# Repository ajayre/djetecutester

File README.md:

# D-Jetronic ECU Tester

A board for testing D-Jetronic ECUs installed on Mercedes C/R107 vehicles.

No warranty, express or implied. Use at your own risk.

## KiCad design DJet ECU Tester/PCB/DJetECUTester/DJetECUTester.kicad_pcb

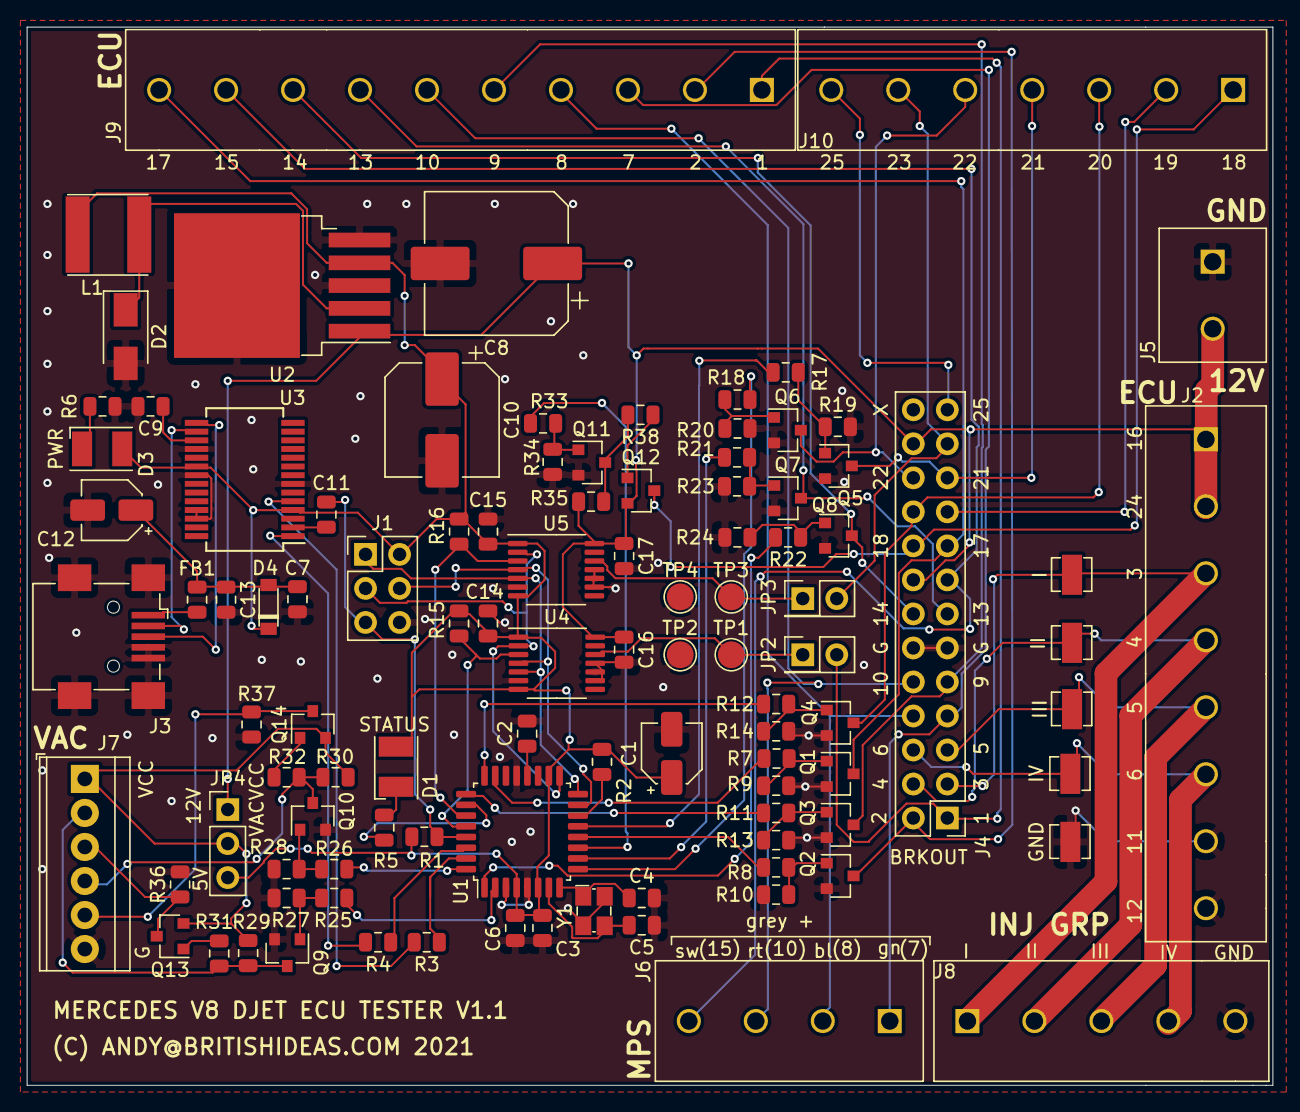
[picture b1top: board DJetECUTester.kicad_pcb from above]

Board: 2 copper layers, 93.0 x 79.0 mm, 103 parts (0 on the bottom side), 81 nets.

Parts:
C1: 4.7uF e; CP_Elec_4x5.8
C2, C9, C11, C13, C14, C15, C16, C17: 100nF; C_0805_2012Metric
C3, C6: 1uF; C_0805_2012Metric
C4, C5: 18pF; C_0805_2012Metric
C7: 10nF; C_0805_2012Metric
C8: 680uF e; CP_Elec_10x10.5
C10: 220uF e; CP_Elec_8x6.5
C12: 4.7uF 16V e; CP_Elec_4x5.8
D1: RED; LED_PLCC-2
D2: B360A-13-F; D_SMA
D3: PWR; LED_PLCC-2
D4: MBR0520LT1G; SOD-123
FB1: MI0805K400R-10; R_0805_2012Metric
J1: ISP; PinHeader_2x03_P2.54mm_Vertical
J2: ECU1; PhoenixContact_COMBICON_PT_8
J3: USB_B_Mini; USB_Mini-B_Wuerth_65100516121_Horizontal
J4: BREAKOUT; PinHeader_2x13_P2.54mm_Vertical
J5: 12V IN; PhoenixContact_COMBICON_MKDSN_2
J6: MPS; PhoenixContact_COMBICON_PT_4
J7: VAC; TerminalBlock_TE_282834-6_1x06_P2.54mm_Horizontal
J8: INJECTORS; PhoenixContact_COMBICON_PT_5
J9: ECU2; PhoenixContact_COMBICON_PT_10
J10: ECU3; PhoenixContact_COMBICON_PT_7
JP2: AIRTEMP; PinHeader_2x01_P2.54mm_Vertical
JP3: COOLANTTEMP; PinHeader_2x01_P2.54mm_Vertical
JP4: VAC VCC; PinHeader_1x03_P2.54mm_Vertical
L1: 33uH; Wurth-WE-LQS-Inductor
Q1, Q2, Q3, Q4, Q5, Q6, Q7, Q8, Q9, Q10, Q11: MMBT2222ALT1G; SOT-23
Q12, Q13, Q14: MMBT3906LT1G; SOT-23
R1, R2, R3, R4, R5, R6: 1K; R_0805_2012Metric
R7, R8, R11, R12, R17, R18, R21, R22, R25, R26, R31, R32, R33, R38: 1k; R_0805_2012Metric
R9, R10, R13, R14, R19, R20, R23, R24, R27, R28, R29, R30, R34, R35, R36, R37: 10k; R_0805_2012Metric
R15, R16: 100k; R_0805_2012Metric
TP1, TP2, TP3, TP4: TestPoint; TestPoint_Pad_D2.0mm
TP5, TP6, TP7, TP8: 5194TR; 5190TR-Colored-Test-Point
TP9: 5195TR; 5190TR-Colored-Test-Point
U1: ATmega328P; LQFP-32_7x7mm_P0.8mm
U2: LM2596S-5; TO-263-5_TabPin3
U3: FT232RL; SSOP-28_5.3x10.2mm_P0.65mm
U4, U5: MCP41HV51-502E-ST; TSSOP-14_4.4x5mm_P0.65mm
Y1: FA-238 16.0000MB-C3; FA-238

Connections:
+3V3: C9.1, U3.17
+5V: C1.1, C3.1, C6.1, C10.1, C14.1, C15.1, D1.2, D3.2, D4.1, J1.2, JP4.3, L1.2, R1.1, R2.1, R15.1, R16.1, U1.4, U1.6, U1.18, U2.4, U3.4, U3.20, U4.1, U4.7, U5.1, U5.7
+12V: C8.1, C16.1, C17.1, J2.1, J2.2, J4.16, J4.24, J5.2, JP4.1, Q12.2, R35.1, U2.1, U4.14, U5.14
/ECU_AIRTEMP-1: J4.1, J9.1, JP2.2
/ECU_COOLANTTEMP-23: J4.23, J10.6, JP3.2
/ECU_DIAGGROUP13-25: J4.25, J10.7
/ECU_FUELPUMPRELAY-19: J4.19, J10.2
/ECU_INJGROUP1-3: J2.3, J4.3, J8.1, TP5.1
/ECU_INJGROUP2-4: J2.4, J4.4, J8.2, TP6.1
/ECU_INJGROUP3-5: J2.5, J4.5, J8.3, TP7.1
/ECU_INJGROUP4-6: J2.6, J4.6, J8.4, TP8.1
/ECU_START-18: J4.18, J10.1, Q12.3
/ECU_TPSACCEL1-9: J4.9, J9.5, Q3.3
/ECU_TPSACCEL2-20: J4.20, J10.3, Q4.3
/ECU_TPSIDLE-17: J4.17, J9.10, Q1.3
/ECU_TPSWOT-2: J4.2, J9.2, Q2.3
/ECU_TRIGGERGROUP1-21: J4.21, J10.4, Q5.3
/ECU_TRIGGERGROUP2-13: J4.13, J9.7, Q7.3
/ECU_TRIGGERGROUP3-22: J4.22, J10.5, Q6.3
/ECU_TRIGGERGROUP4-14: J4.14, J9.8, Q8.3
/MISO: J1.1, U1.16, U4.5, U5.5
/MOSI: J1.4, U1.15, U4.4, U5.4
/MPS-7: J4.7, J6.1, J9.3
/MPS-8: J4.8, J6.2, J9.4
/MPS-10: J4.10, J6.3, J9.6
/MPS-15: J4.15, J6.4, J9.9
/RX: R4.2, U3.1
/SCK: J1.3, U1.17, U4.2, U5.2
/START: R33.2, U1.11
/STATUS: R5.2, U1.26
/TPSACCEL1: R11.2, U1.25
/TPSACCEL2: R12.2, U1.24
/TPSIDLE: R7.2, U1.23
/TPSWOT: R8.2, U1.12
/TRIGGERGROUP1: R17.2, U1.13
/TRIGGERGROUP2: R18.2, U1.9
/TRIGGERGROUP3: R21.2, U1.10
/TRIGGERGROUP4: R22.2, U1.1
/TX: R3.2, U3.5
/VAC1: R25.2, U1.2
/VAC2: R26.2, U1.32
/Vacuum/VACVCC: J7.1, JP4.2, Q13.2, Q14.2, R29.1, R30.1
/~AIRTEMP_CS: R15.2, U1.28, U4.3
/~COOLANTTEMP_CS: R16.2, U1.27, U5.3
/~RESET: C11.1, J1.5, R1.2, U1.29
GND: C1.2, C2.2, C3.2, C4.2, C5.1, C6.2, C7.1, C8.2, C9.2, C10.2, C12.2, C13.2, C14.2, C15.2, C16.2, C17.2, D2.2, J1.6, J2.7, J2.8, J3.4, J3.5, J3.6, J4.11, J4.12, J5.1, J7.6, J8.5, Q1.2, Q2.2, Q3.2, Q4.2, Q5.2, Q6.2, Q7.2, Q8.2, Q9.2, Q10.2, Q11.2, R6.1, R9.2, R10.2, R13.2, R14.2, R19.2, R20.2, R23.2, R24.2, R27.2, R28.2, R34.2, R36.2, R37.2, TP2.1, TP4.1, TP9.1, U1.3, U1.5, U1.21, U2.3, U2.5, U3.7, U3.18, U3.21, U3.25, U3.26, U4.6, U4.9, U4.10, U4.11, U5.6, U5.9, U5.10, U5.11, Y1.2, Y1.4
unnamed: C2.1, U1.20
unnamed: C4.1, U1.8, Y1.1
unnamed: C5.2, U1.7, Y1.3
unnamed: C11.2, U3.2
unnamed: D1.1, R5.1
unnamed: D2.1, L1.1, U2.2
unnamed: D3.1, R6.2
unnamed: FB1.1, J3.1
unnamed: J3.2, U3.16
unnamed: J3.3, U3.15
unnamed: J7.2, Q9.3, R29.2, R31.2
unnamed: J7.3, Q13.3, R36.1
unnamed: J7.4, Q10.3, R30.2, R32.2
unnamed: J7.5, Q14.3, R37.1
unnamed: JP2.1, TP1.1, U4.12
unnamed: JP3.1, TP3.1, U5.12
unnamed: Q1.1, R7.1, R9.1
unnamed: Q2.1, R8.1, R10.1
unnamed: Q3.1, R11.1, R13.1
unnamed: Q4.1, R12.1, R14.1
unnamed: Q5.1, R17.1, R19.1
unnamed: Q6.1, R18.1, R20.1
unnamed: Q7.1, R21.1, R23.1
unnamed: Q8.1, R22.1, R24.1
unnamed: Q9.1, R25.1, R27.1
unnamed: Q10.1, R26.1, R28.1
unnamed: Q11.1, R33.1, R34.1
unnamed: Q11.3, R35.2, R38.2
unnamed: Q12.1, R38.1
unnamed: Q13.1, R31.1
unnamed: Q14.1, R32.1
unnamed: R2.2, U1.14
unnamed: R3.1, U1.31
unnamed: R4.1, U1.30
VBUS: C7.2, C12.1, C13.1, D4.2, FB1.2

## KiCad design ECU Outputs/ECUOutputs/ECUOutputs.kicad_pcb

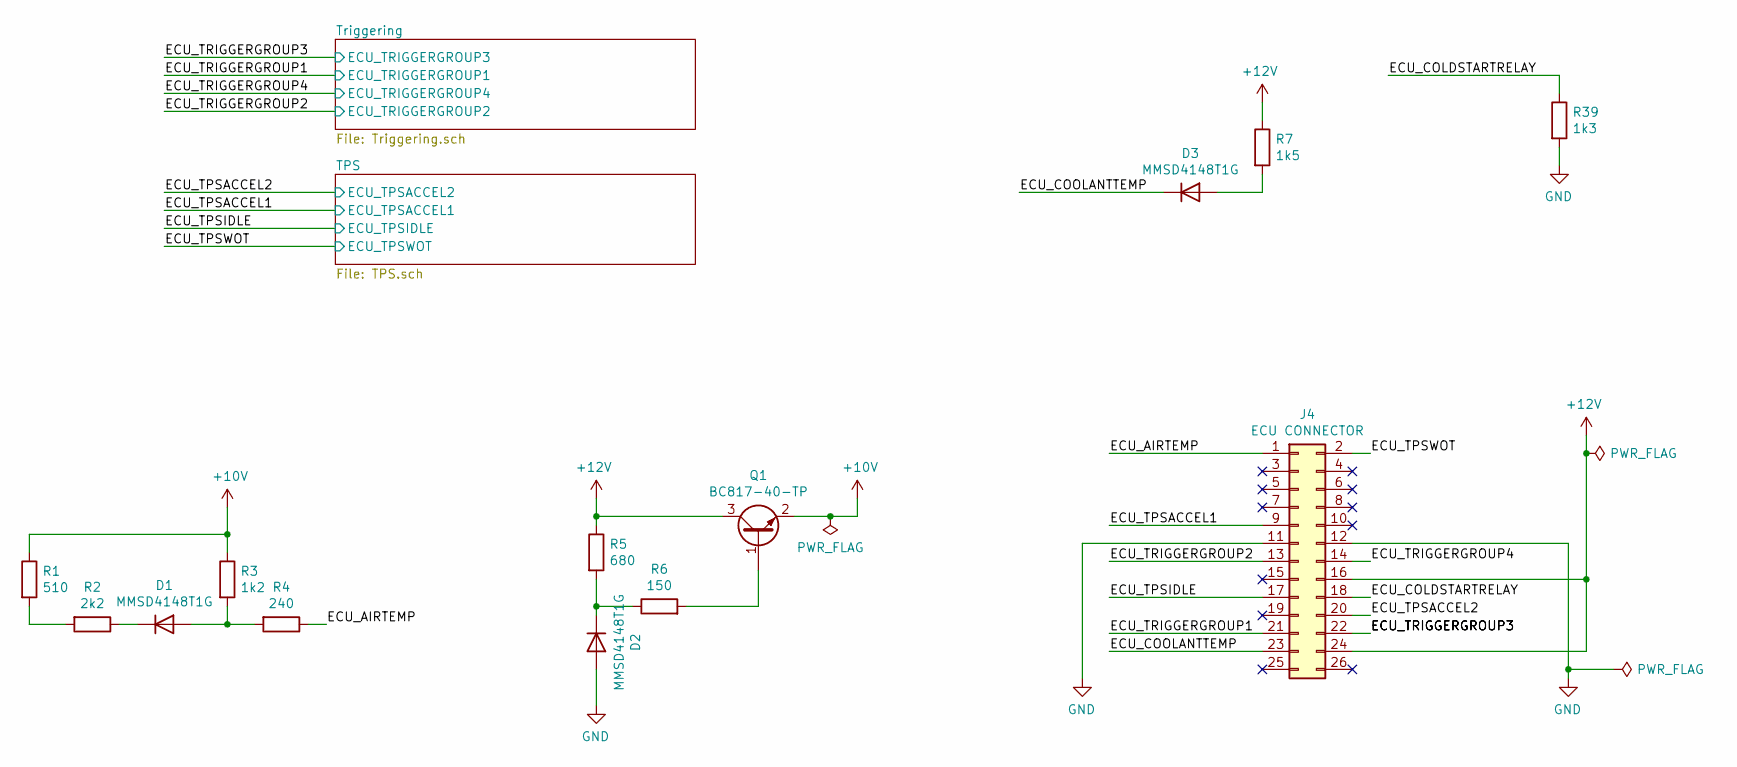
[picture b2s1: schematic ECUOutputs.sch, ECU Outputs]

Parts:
D1, D2, D3: MMSD4148T1G; D_SOD-123
J4: ECU CONNECTOR; IDC-Header_2x13_P2.54mm_Vertical
Q1: BC817-40-TP; SOT-23
R1: 510; R_0805_2012Metric
R2: 2k2; R_0805_2012Metric
R3: 1k2; R_0805_2012Metric
R4: 240; R_0805_2012Metric
R5: 680; R_0805_2012Metric
R6: 150; R_0805_2012Metric
R7: 1k5; R_0805_2012Metric
R39: 1k3; R_0805_2012Metric

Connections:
+10V: Q1.2 (E), R1.1, R3.1; also elsewhere on the board
+12V: J4.16, J4.24, Q1.3 (C), R5.1, R7.1; also elsewhere on the board
/ECU_AIRTEMP: J4.1, R4.1
/ECU_COLDSTARTRELAY: J4.18, R39.1
/ECU_COOLANTTEMP: D3.1 (K), J4.23
/ECU_TPSACCEL1: J4.9; also elsewhere on the board
/ECU_TPSACCEL2: J4.20; also elsewhere on the board
/ECU_TPSIDLE: J4.17; also elsewhere on the board
/ECU_TPSWOT: J4.2; also elsewhere on the board
/ECU_TRIGGERGROUP1: J4.21; also elsewhere on the board
/ECU_TRIGGERGROUP2: J4.13; also elsewhere on the board
/ECU_TRIGGERGROUP3: J4.22; also elsewhere on the board
/ECU_TRIGGERGROUP4: J4.14; also elsewhere on the board
GND: D2.2 (A), J4.11, J4.12, R39.2; also elsewhere on the board
unnamed: D1.1 (K), R2.1
unnamed: D1.2 (A), R3.2, R4.2
unnamed: D2.1 (K), R5.2, R6.1
unnamed: D3.2 (A), R7.2
unnamed: Q1.1 (B), R6.2
unnamed: R1.2, R2.2

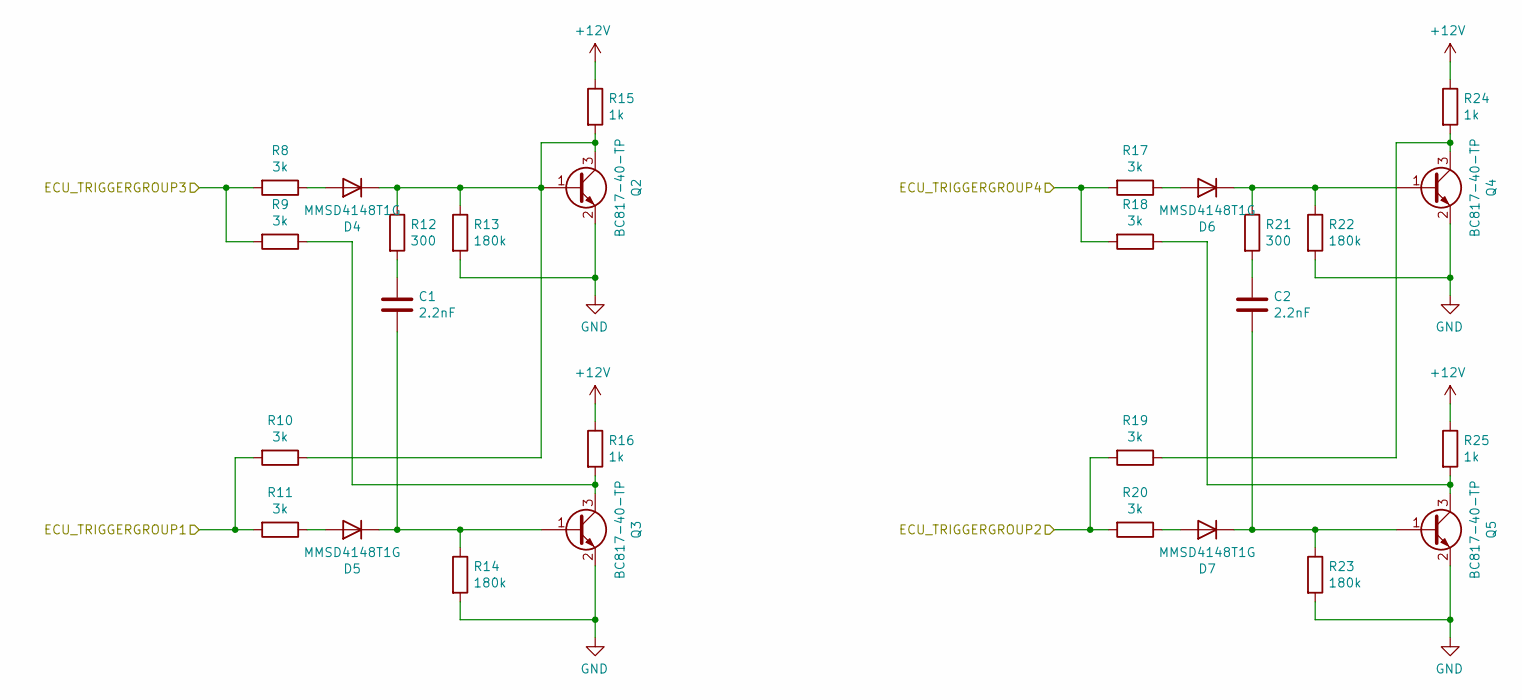
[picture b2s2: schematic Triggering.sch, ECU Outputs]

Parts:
C1, C2: 2.2nF; C_0805_2012Metric
D4, D5, D6, D7: MMSD4148T1G; D_SOD-123
Q2, Q3, Q4, Q5: BC817-40-TP; SOT-23
R8, R9, R10, R11, R17, R18, R19, R20: 3k; R_0805_2012Metric
R12, R21: 300; R_0805_2012Metric
R13, R14, R22, R23: 180k; R_0805_2012Metric
R15, R16, R24, R25: 1k; R_0805_2012Metric

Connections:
+12V: R15.1, R16.1, R24.1, R25.1; also elsewhere on the board
/ECU_TRIGGERGROUP1: R10.2, R11.2; also elsewhere on the board
/ECU_TRIGGERGROUP2: R19.2, R20.2; also elsewhere on the board
/ECU_TRIGGERGROUP3: R8.2, R9.2; also elsewhere on the board
/ECU_TRIGGERGROUP4: R17.2, R18.2; also elsewhere on the board
GND: Q2.2 (E), Q3.2 (E), Q4.2 (E), Q5.2 (E), R13.2, R14.2, R22.2, R23.2; also elsewhere on the board
unnamed: C1.1, R12.2
unnamed: C1.2, D5.1 (K), Q3.1 (B), R14.1
unnamed: C2.1, R21.2
unnamed: C2.2, D7.1 (K), Q5.1 (B), R23.1
unnamed: D4.1 (K), Q2.1 (B), Q2.3 (C), R10.1, R12.1, R13.1, R15.2
unnamed: D4.2 (A), R8.1
unnamed: D5.2 (A), R11.1
unnamed: D6.1 (K), Q4.1 (B), R21.1, R22.1
unnamed: D6.2 (A), R17.1
unnamed: D7.2 (A), R20.1
unnamed: Q3.3 (C), R9.1, R16.2
unnamed: Q4.3 (C), R19.1, R24.2
unnamed: Q5.3 (C), R18.1, R25.2

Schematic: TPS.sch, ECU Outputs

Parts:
C3: 3.3nF
D8, D9, D10, D11, D12: D
Q6, Q7: Q_NPN_BCE
Q8: Q_PNP_BCE
R26, R29: 3k
R27, R28: 10k
R30, R31: 180k
R32: 300
R33, R34: 1k8
R35: 47k
R36: 5k1
R37: 22k
R38: 6k2

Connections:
+10V: Q8.3, R36.1, R37.1; also elsewhere on the board
+12V: R33.1, R34.1; also elsewhere on the board
/ECU_TPSACCEL1: R28.2, R29.2; also elsewhere on the board
/ECU_TPSACCEL2: R26.2, R27.2; also elsewhere on the board
/ECU_TPSIDLE: D11.1 (K), D12.1 (K); also elsewhere on the board
/ECU_TPSWOT: R36.2; also elsewhere on the board
GND: D11.2 (A), Q6.2, Q7.2, R30.2, R31.2, R38.2; also elsewhere on the board
unnamed: C3.1, R32.2
unnamed: C3.2, D10.1 (K), Q7.1, R31.1
unnamed: D8.1 (K), Q6.1, R30.1, R32.1
unnamed: D8.2 (A), R26.1
unnamed: D9.2 (A), R29.1
unnamed: D9.1 (K), D10.2 (A)
unnamed: D12.2 (A), R35.1
unnamed: Q6.3, R28.1, R33.2
unnamed: Q7.3, R27.1, R34.2
unnamed: Q8.1, R35.2, R37.2
unnamed: Q8.2, R38.1

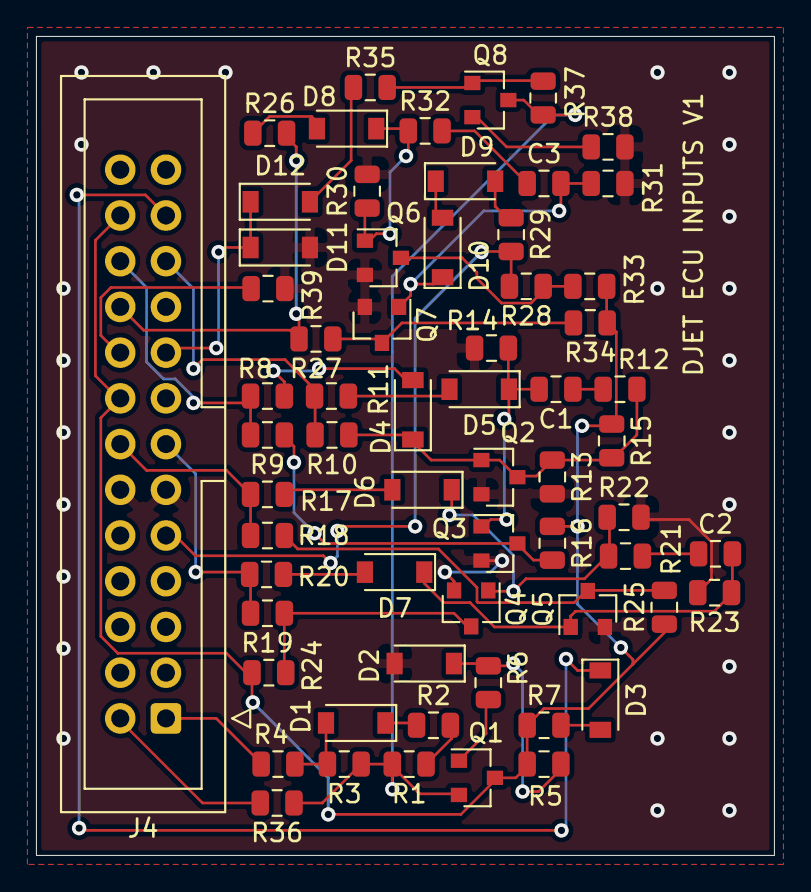
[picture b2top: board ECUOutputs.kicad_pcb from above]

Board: 2 copper layers, 41.0 x 45.5 mm, 63 parts (0 on the bottom side), 44 nets.

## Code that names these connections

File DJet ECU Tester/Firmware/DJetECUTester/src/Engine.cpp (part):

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// pins
#define PIN_STATUS_LED    A3  // PC3
#define PIN_START         7   // PD7
#define PIN_TPSWOT        8   // PB0
#define PIN_TPSIDLE       A0  // PC0
#define PIN_TPSACCEL1     A2  // PC2
#define PIN_TPSACCEL2     A1  // PC1
#define PIN_VAC1          4   // PD4
#define PIN_VAC2          2   // PD2
#define PIN_AIRTEMPCS     A5  // PC5
#define PIN_COOLANTTEMPCS A4  // PC4

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#define PORT_TRIGGERGROUP3 PORTD
#define PORT_TRIGGERGROUP4 PORTD

#define PIN_TRIGGERGROUP1 1
#define PIN_TRIGGERGROUP2 6
#define PIN_TRIGGERGROUP3 5
#define PIN_TRIGGERGROUP4 3

#define DIR_TRIGGERGROUP1 DDRB
#define DIR_TRIGGERGROUP2 DDRD
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#define STARTING               digitalWrite(PIN_START, HIGH);
#define NOTSTARTING            digitalWrite(PIN_START, LOW);

#define TPS_WOT                digitalWrite(PIN_TPSWOT, HIGH);
#define TPS_NOTWOT             digitalWrite(PIN_TPSWOT, LOW);

#define TPS_IDLE               digitalWrite(PIN_TPSIDLE, HIGH);
#define TPS_NOTIDLE            digitalWrite(PIN_TPSIDLE, LOW);

#define TPS_ACCEL1_ASSERT      digitalWrite(PIN_TPSACCEL1, HIGH);
#define TPS_ACCEL1_DEASSERT    digitalWrite(PIN_TPSACCEL1, LOW);

#define TPS_ACCEL2_ASSERT      digitalWrite(PIN_TPSACCEL2, HIGH);
#define TPS_ACCEL2_DEASSERT    digitalWrite(PIN_TPSACCEL2, LOW);

#define VAC1_ASSERT            digitalWrite(PIN_VAC1, HIGH);
#define VAC1_DEASSERT          digitalWrite(PIN_VAC1, LOW);

#define VAC2_ASSERT            digitalWrite(PIN_VAC2, HIGH);
#define VAC2_DEASSERT          digitalWrite(PIN_VAC2, LOW);

#define AIRTEMPCS_DEASSERT     digitalWrite(PIN_AIRTEMPCS, HIGH);
#define COOLANTTEMPCS_DEASSERT digitalWrite(PIN_COOLANTTEMPCS, HIGH);

#define TRIGGERGROUP1_HIGH (PORT_TRIGGERGROUP1 &= ~(1 << PIN_TRIGGERGROUP1))
#define TRIGGERGROUP1_LOW  (PORT_TRIGGERGROUP1 |=  (1 << PIN_TRIGGERGROUP1))
#define TRIGGERGROUP2_HIGH (PORT_TRIGGERGROUP2 &= ~(1 << PIN_TRIGGERGROUP2))
#define TRIGGERGROUP2_LOW  (PORT_TRIGGERGROUP2 |=  (1 << PIN_TRIGGERGROUP2))
#define TRIGGERGROUP3_HIGH (PORT_TRIGGERGROUP3 &= ~(1 << PIN_TRIGGERGROUP3))
#define TRIGGERGROUP3_LOW  (PORT_TRIGGERGROUP3 |=  (1 << PIN_TRIGGERGROUP3))
#define TRIGGERGROUP4_HIGH (PORT_TRIGGERGROUP4 &= ~(1 << PIN_TRIGGERGROUP4))
#define TRIGGERGROUP4_LOW  (PORT_TRIGGERGROUP4 |=  (1 << PIN_TRIGGERGROUP4))

#define ASSERT   1
#define DEASSERT 0
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  STATUS_LED_OFF;
  pinMode(PIN_START,         OUTPUT);
  NOTSTARTING;
  DIR_TRIGGERGROUP1 |= (1 << PIN_TRIGGERGROUP1);
  TRIGGERGROUP1_HIGH;
  DIR_TRIGGERGROUP2 |= (1 << PIN_TRIGGERGROUP2);
  TRIGGERGROUP2_HIGH;
  DIR_TRIGGERGROUP3 |= (1 << PIN_TRIGGERGROUP3);
  TRIGGERGROUP3_HIGH;
  DIR_TRIGGERGROUP4 |= (1 << PIN_TRIGGERGROUP4);
  TRIGGERGROUP4_HIGH;
  pinMode(PIN_TPSWOT,        OUTPUT);
  TPS_NOTWOT;
  pinMode(PIN_TPSIDLE,       OUTPUT);
  TPS_NOTIDLE;
  pinMode(PIN_TPSACCEL1,     OUTPUT);
  TPS_ACCEL1_DEASSERT;
  pinMode(PIN_TPSACCEL2,     OUTPUT);
  TPS_ACCEL2_DEASSERT;
  pinMode(PIN_VAC1,          OUTPUT);
  VAC1_DEASSERT;
  pinMode(PIN_VAC2,          OUTPUT);
  VAC2_DEASSERT;
  pinMode(PIN_AIRTEMPCS,     OUTPUT);
  AIRTEMPCS_DEASSERT;
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
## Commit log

2021-03-06 Started work on an ECU tester.
2021-03-06 Added injector waveform test points.
2021-03-09 Working on ECU tester and ECU outputs board.
2021-03-09 Started work on PCB.
2021-03-10 Working on PCB layout. Changed CSV circuit from optocoupler to transistors. Added decoupling caps for digital pots.
2021-03-10 Corrected mistake in flip-flop copied from 005 ECU schematic.
2021-03-10 Empty project for firmware.
2021-03-12 Working on PCB layout
2021-03-12 Adding 3D models.
2021-03-12 Added final 3D models.
2021-03-14 Added simulation of injector drivers - only 1-5 group tested.
2021-03-14 Updated injector driver simulation to make measuring current consumption easier.
2021-03-14 Increased injectors from four to eight. Added current measurement for injector groups.
2021-03-15 Added connector for injector groups.
2021-03-15 Updated manufacturer part numbers. Working on ECU outputs tester board.
2021-03-16 Added resistor to tester. Generated manufacturing files.
2021-03-16 Laid out ECU outputs PCB. Generated manufacturing files.
2021-03-16 Started work on firmware.
2021-03-18 Working on menu system.
2021-03-19 Working on menu.
2021-03-19 Completed UI.
2021-03-19 Minor cleanup
2021-03-19 Refactoring.
2021-03-19 Minor twweak.
2021-03-20 Removed cold start valve - this appears to be an output from the ECU so we can't control it.
2021-03-21 Added engine cranking. Added support for backspace.
2021-03-21 Renamed CSV to Start. Added PDF version of schematics.
2021-03-21 Added enrichment pulses.
2021-03-22 Added Steinhart-Hart models for temperature sensors. Adapted from Brad's spreadsheets.
2021-03-22 Updated datasheets.
2021-03-23 Added library for MCP4xxx.
2021-03-23 Added library to control timer 1.
2021-03-24 Added pulse generator.
2021-03-24 Added spreadsheets for thermistor models from Brad Cushman.
2021-03-25 Fixed bugs. Changed angle to dwell.
2021-03-28 Added jig for installing pin headers.
2021-04-04 Updated temperature support - untested. Switched to Arduino "new" bootloader.
2021-04-05 Worked around mistake in schematic that swapped trigger groups 2 and 3.
2021-04-07 Working on version 1.1
2021-04-08 Completed first attempt at new layout.
2021-04-08 Added D-Jetronic text and stiching vias.
2021-04-09 Updated manufacturing files.
2021-04-11 Better performance for trigger pulse generator.
2021-04-21 Updated 3D model. Added 3D printed Base. LED now flashes faster when engine is running.
2021-04-21 Updated Schematic Removed gcode file.
2021-04-25 Version 1.00
2021-06-06 Improved TPS implementation to generate all of the enrichment pulses when increasing throttle. Always goes back to default throttle enrichment settings for zero throttle. No longer asks for up or dow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
2021-06-19 Added verbose mode to upload.
2021-06-19 Added avrdude and programming instructions.
2021-06-19 Updated programming instructions.
2021-06-19 Added release.
2021-06-29 Rewrote pulse generator to fix bugs with duty cycle.
2021-06-29 Created V3 release. Added 3D files.
2021-07-12 Inverted operation of pulse generator waveforms.
2021-07-12 Generated new release.
2021-07-13 Version 5 Added debug output for pulse generator.
2021-07-13 Reverted back to r56. The debug output added for r57 was not needed.
2021-07-13 Set minimum PG dwell to 39 degrees. This corresponds to a 1ms pulse at 6,500 RPM.
2021-07-13 Increased max PG dwell to 321 degrees.
2021-07-13 Added new release.
2021-07-23 Added start of CloneECU project.
2021-07-23 Removed components external to the ECU. Changed text blocks. Passes the electrical DRC.
2021-07-25 Moved CloneECU to it's own repo.
2021-07-25 Removed old project.
2021-07-25 Removed old notes.
2021-07-26 Create LICENSE
2021-08-01 Added more current measurements to injector driver simulation.
2022-08-02 Updated ECU connector drawing and added color to 3D model.
2022-09-22 Updated to use new TPS throttle % settings.
